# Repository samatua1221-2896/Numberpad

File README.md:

# Numberpad

This is a 10 key hackpad that I just wanted to try and make based on a standard numberpad. This is my first experience working with making custom pcbs and a deeper use of CAD in general.

## CAD

This is a pretty basic case made using Onshape, basically able to surround all of the keys and have a visual of the XIAO RP2040 itself.

## PCB

This was my first time really delving into the usage of custom PCBs and KiCad as well. There is no matrix since all the keys are wired directly to their own pins.

## BOM

- 4x Cherry MX Switches
- 4x M3x16mm screws
- 1x XIAO RP2040
- 1x 3D Printed Case
  - Top and Bottom Parts

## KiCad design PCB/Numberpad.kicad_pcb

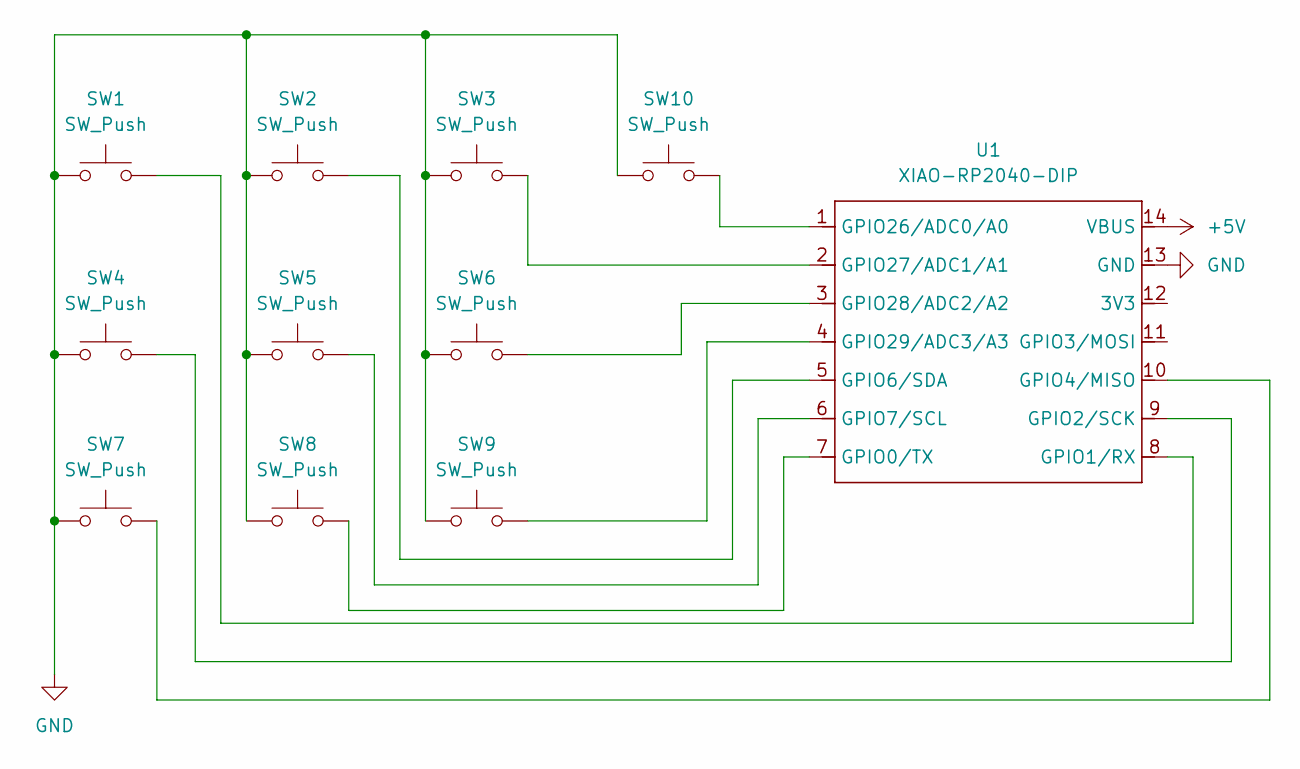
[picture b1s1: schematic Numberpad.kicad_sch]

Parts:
SW1, SW2, SW3, SW4, SW5, SW6, SW7, SW8, SW9, SW10: SW_Push; SW_Cherry_MX_1.00u_PCB
U1: XIAO-RP2040-DIP

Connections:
+5V: U1.14 (VBUS)
GND: SW1.1, SW2.1, SW3.1, SW4.1, SW5.1, SW6.1, SW7.1, SW8.1, SW9.1, SW10.1, U1.13 (GND)
unnamed: SW8.2, U1.7 (GPIO0/TX)
unnamed: SW1.2, U1.8 (GPIO1/RX)
unnamed: SW4.2, U1.9 (GPIO2/SCK)
unnamed: SW7.2, U1.10 (GPIO4/MISO)
unnamed: SW2.2, U1.5 (GPIO6/SDA)
unnamed: SW5.2, U1.6 (GPIO7/SCL)
unnamed: SW10.2, U1.1 (GPIO26/ADC0/A0)
unnamed: SW3.2, U1.2 (GPIO27/ADC1/A1)
unnamed: SW6.2, U1.3 (GPIO28/ADC2/A2)
unnamed: SW9.2, U1.4 (GPIO29/ADC3/A3)

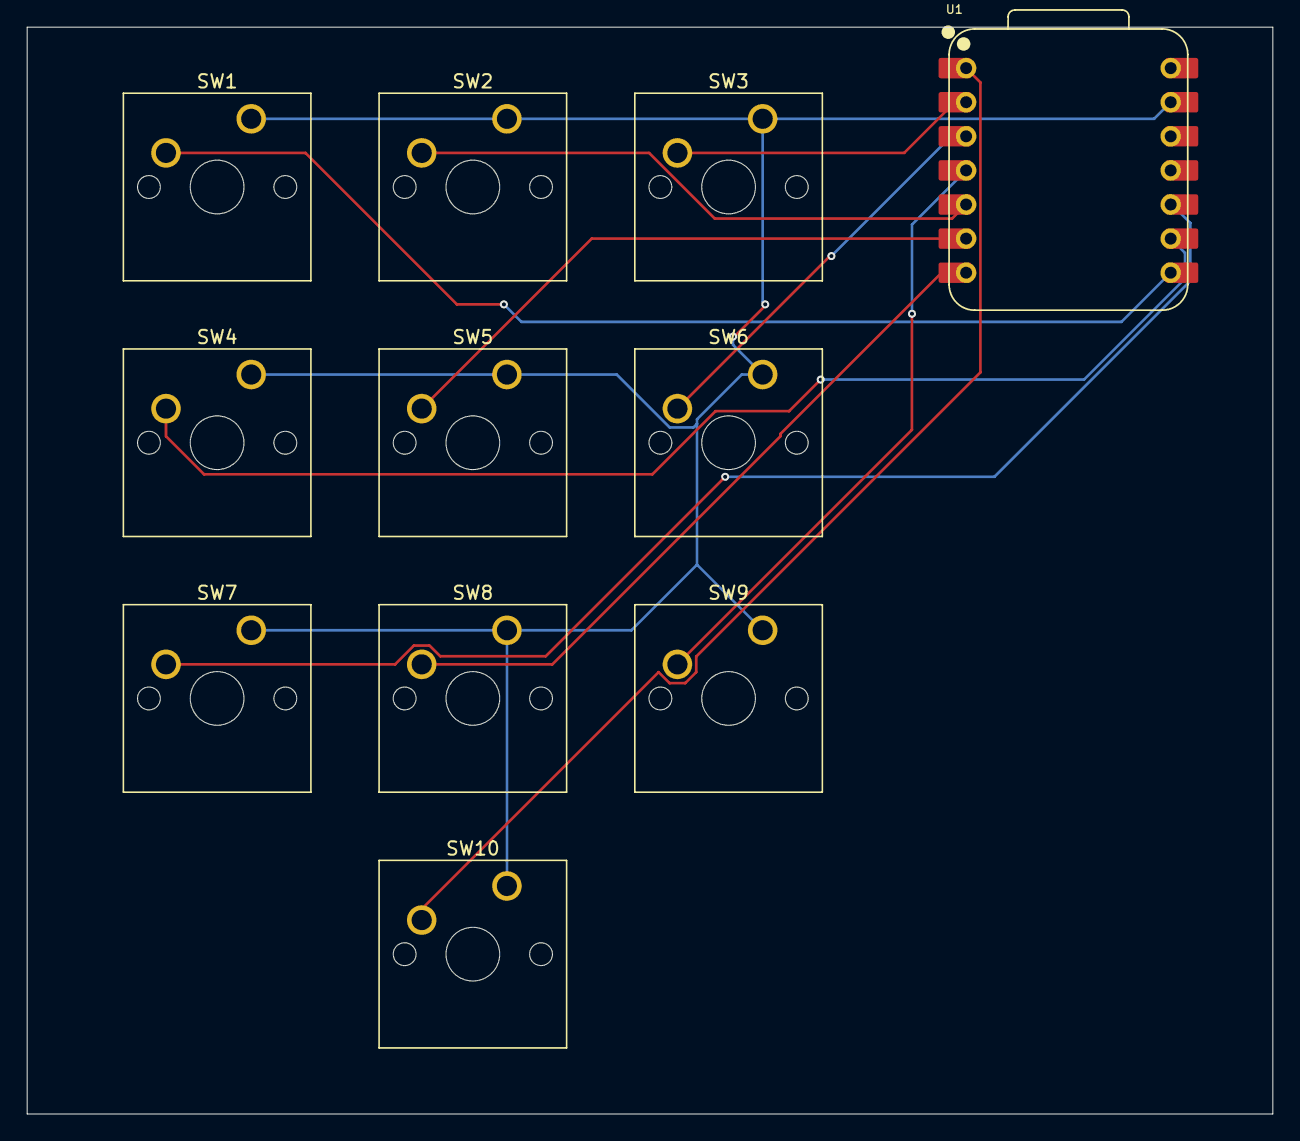
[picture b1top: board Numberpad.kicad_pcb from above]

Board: 2 copper layers, 92.8 x 81.0 mm, 11 parts (0 on the bottom side), 11 nets.

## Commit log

2025-05-27 Create test
2025-05-27 Create test1
